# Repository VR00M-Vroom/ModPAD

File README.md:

# CAD Images

### Exploded View

### Normal View

# Electrical 

## PCB

## Schematic

# Final

# Bill of Materials 
---------------------------------------------------
6x Keyswitches
-
6x Keycaps
-
1x EC11 Rotary Encoder
-
1x Rotary Encoder Cap
-
1x Seeed Studios Xiao RP2040-DIP (With Pinheaders)
-
1x .91 inch OLED 
-

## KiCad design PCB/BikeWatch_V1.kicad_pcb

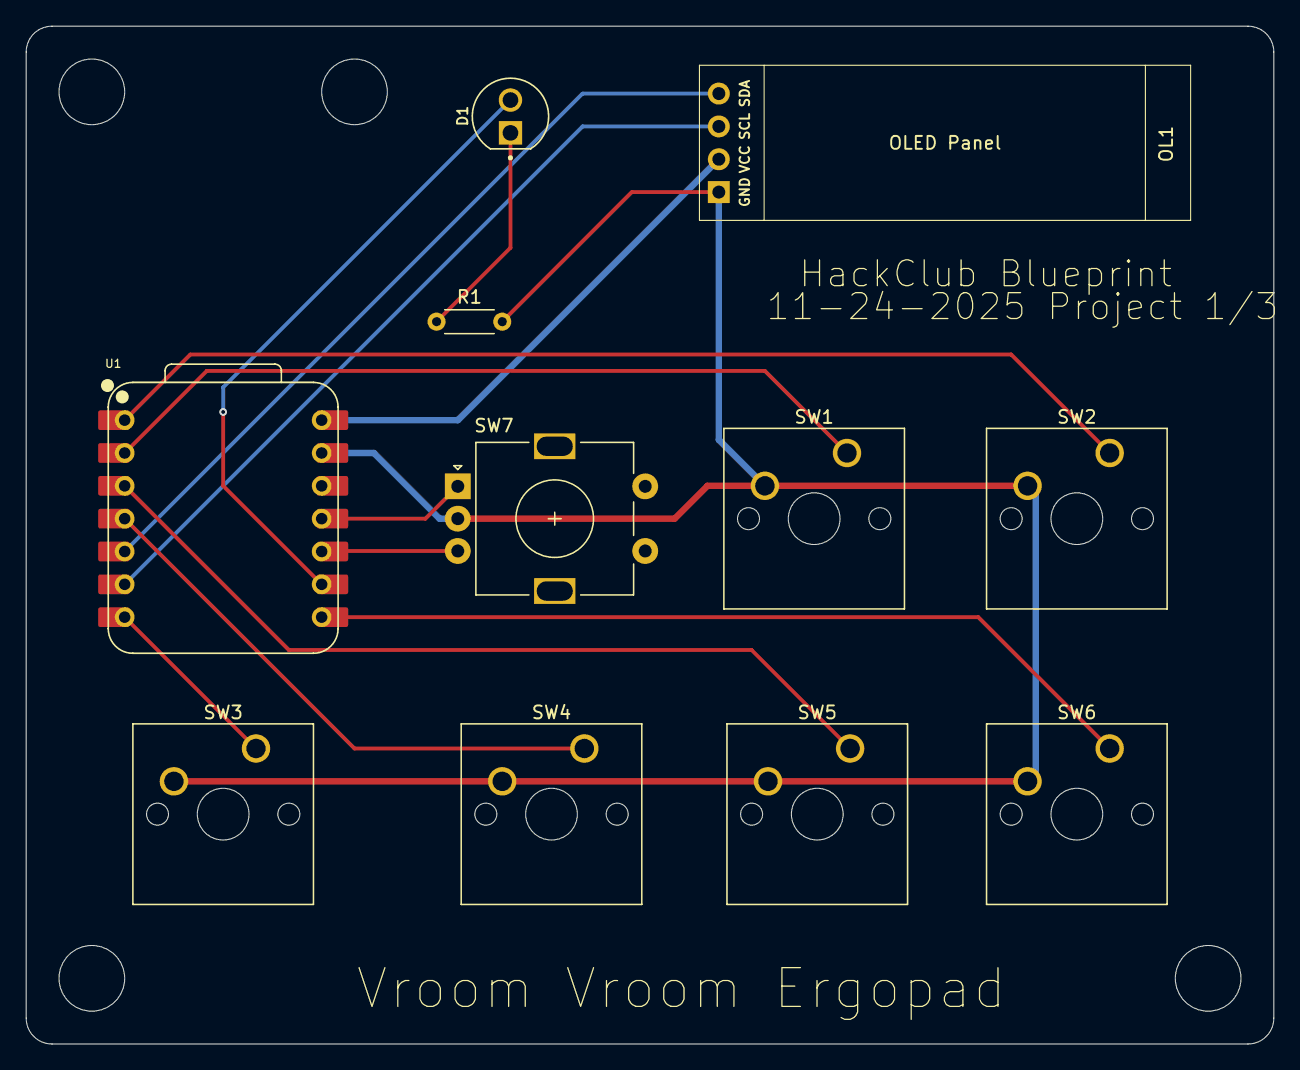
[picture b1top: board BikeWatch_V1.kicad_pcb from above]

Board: 2 copper layers, 96.5 x 78.7 mm, 11 parts (0 on the bottom side), 14 nets.

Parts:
D1: L08R5000Q1; LEDRD254W57D500H1070
OL1: SSD1306_0.91_OLED; SSD1306-0.91-OLED-4pin-128x32
R1: R; R_Axial_DIN0204_L3.6mm_D1.6mm_P5.08mm_Horizontal
SW1, SW2, SW3, SW4, SW5, SW6: SW_Push; SW_Cherry_MX_1.00u_PCB
SW7: RotaryEncoder_Switch; RotaryEncoder_Alps_EC11E-Switch_Vertical_H20mm
U1: XIAO-RP2040-DIP

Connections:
+5V: OL1.2 (VCC), U1.14 (VBUS)
A: SW7.A, U1.11 (GPIO3/MOSI)
B: SW7.B, U1.10 (GPIO4/MISO)
GND: OL1.1 (GND), R1.2, SW1.2, SW2.2, SW3.2, SW4.2, SW5.2, SW6.2, SW7.C, U1.13 (GND)
LED: D1.A, U1.9 (GPIO2/SCK)
unnamed: D1.C, R1.1
SCL: OL1.3 (SCL), U1.6 (GPIO7/SCL)
SDA: OL1.4 (SDA), U1.5 (GPIO6/SDA)
SW1: SW1.1, U1.2 (GPIO27/ADC1/A1)
SW2: SW2.1, U1.1 (GPIO26/ADC0/A0)
SW3: SW3.1, U1.7 (GPIO0/TX)
SW4: SW4.1, U1.4 (GPIO29/ADC3/A3)
SW5: SW5.1, U1.3 (GPIO28/ADC2/A2)
SW6: SW6.1, U1.8 (GPIO1/RX)

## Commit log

2025-11-26 Create CAD
2025-11-26 Add new file 'What' with initial content
2025-11-26 Add new line to PCB/Temp file
2025-11-27 Create Temp
2025-11-27 Create Read Me
2025-11-27 Add section header for CAD Images
2025-11-27 Update Bill of Materials in README
2026-01-03 Update README with final image and schematic
    Added final image to the README and updated schematic section.
